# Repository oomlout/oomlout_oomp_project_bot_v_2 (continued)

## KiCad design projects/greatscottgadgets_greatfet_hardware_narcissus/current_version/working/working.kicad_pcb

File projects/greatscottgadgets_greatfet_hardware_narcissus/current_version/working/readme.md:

# greatfet_hardware
 
## summary 
* id: greatscottgadgets_greatfet_hardware_narcissus
* user: greatscottgadgets
* name: greatfet_hardware
* board: narcissus
* repo: https://github.com/greatscottgadgets/greatfet-hardware
* src_file_repo_kicad_pcb: narcissus/narcissus.kicad_pcb
* src_file_repo_kicad_pcb_link: https://github.com/greatscottgadgets/greatfet-hardware/tree/master/narcissus/narcissus.kicad_pcb

* src_file_repo_sch: narcissus/narcissus.sch
* src_file_repo_sch_link: https://github.com/greatscottgadgets/greatfet-hardware/tree/master/narcissus/narcissus.sch
* full details link: https://github.com/oomlout/oomlout_oomp_project_bot_v_2/tree/main/projects/greatscottgadgets_greatfet_hardware_narcissus/current_version/working

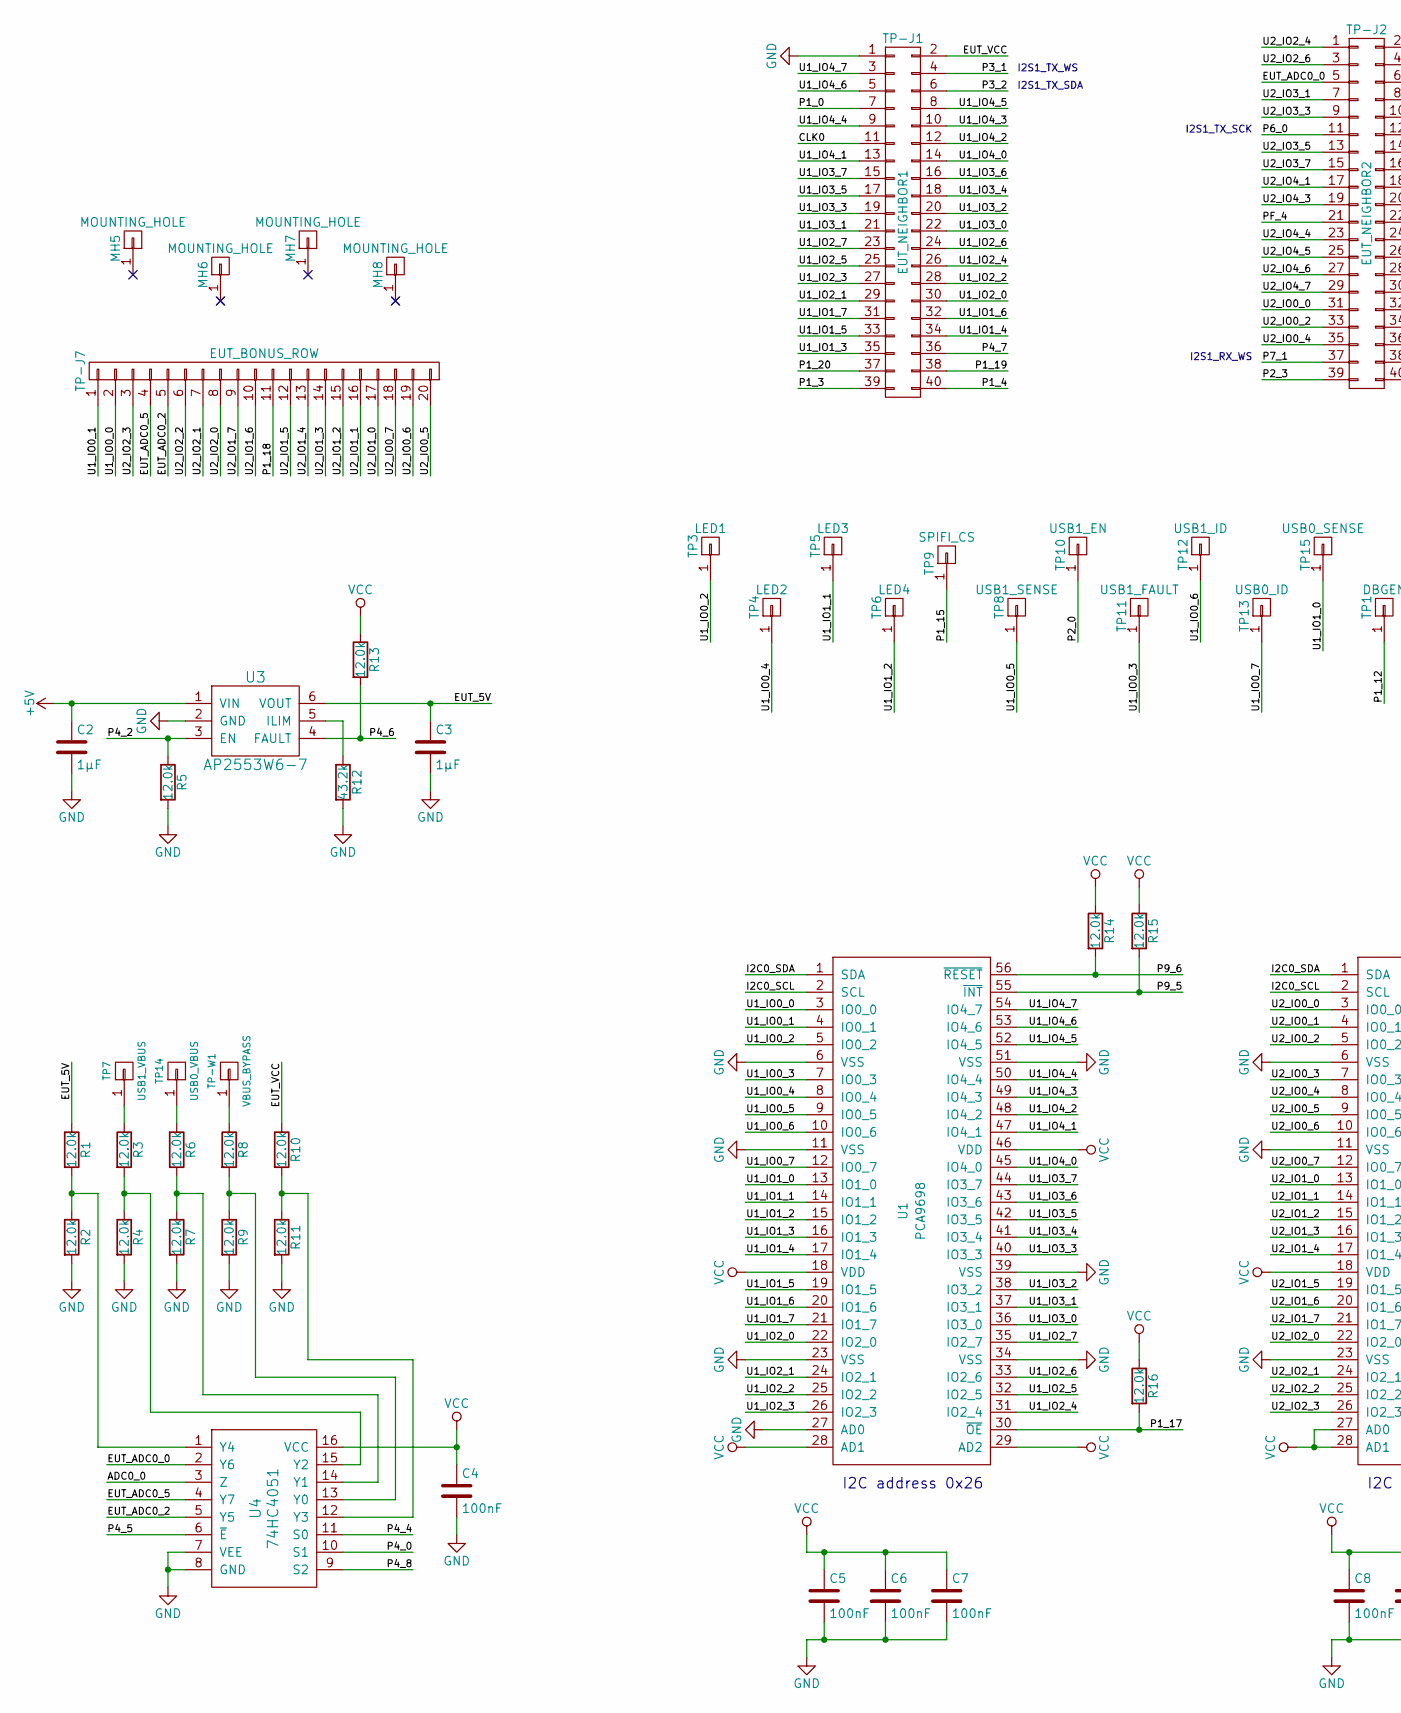
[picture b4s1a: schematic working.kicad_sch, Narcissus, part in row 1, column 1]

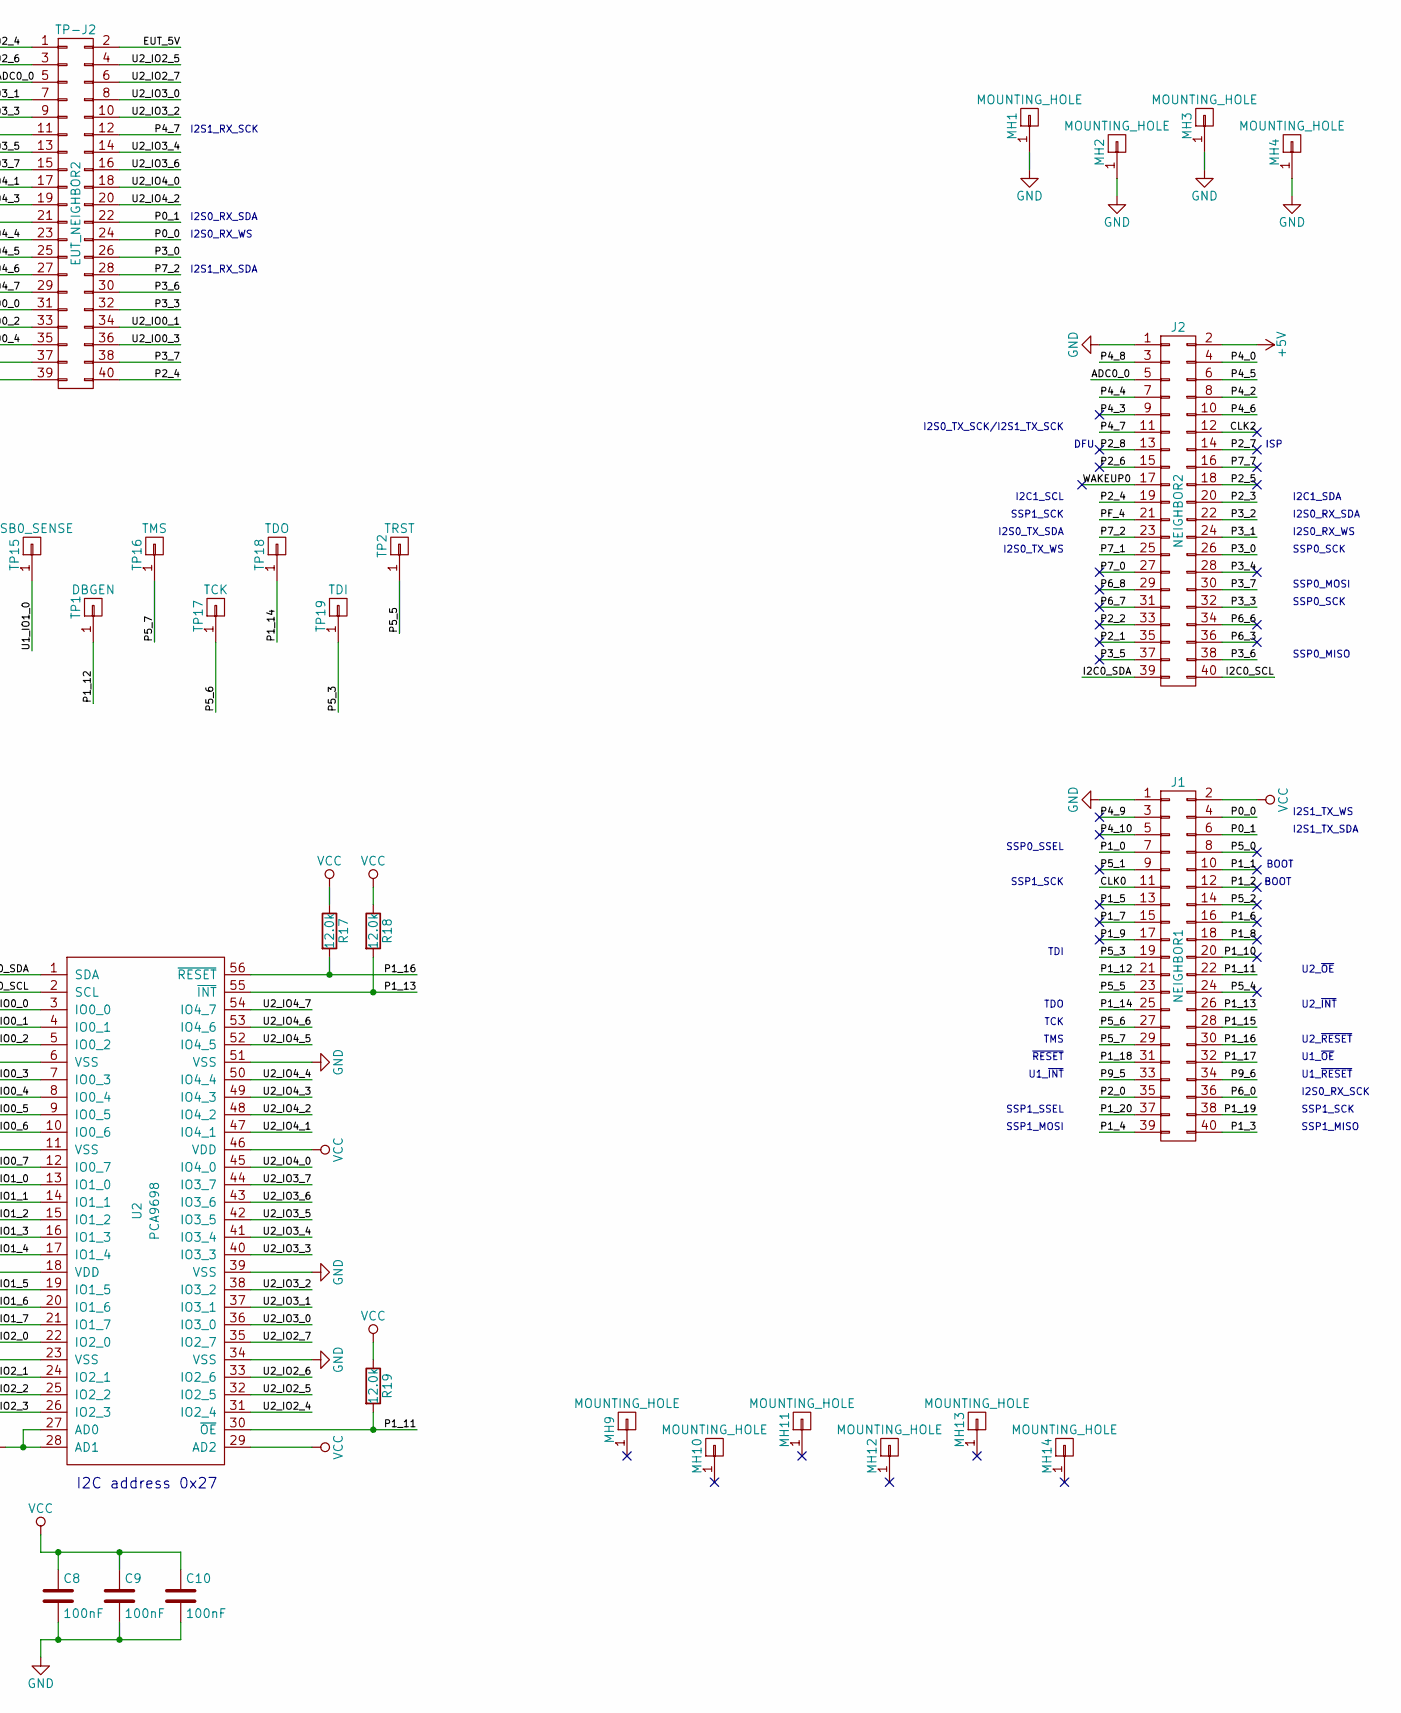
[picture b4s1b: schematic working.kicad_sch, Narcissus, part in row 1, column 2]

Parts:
C2, C3: 1µF; 0603; Part Number CL10A105KP8NNNC
C4, C5, C6, C7, C8, C9, C10: 100nF; 0603; Part Number C0603C104M4RAC
J1: NEIGHBOR1; HEADER-2x20-REVERSE; Part Number SSW-120-01-F-D
J2: NEIGHBOR2; HEADER-2x20-REVERSE; Part Number SSW-120-01-F-D
MH1, MH2, MH3, MH4, MH5, MH6, MH7, MH8, MH9, MH10, MH11, MH12, MH13, MH14: MOUNTING_HOLE; HOLE126MIL-COPPER
R1, R2, R3, R4, R5, R6, R7, R8, R9, R10, R11, R13, R14, R15, R16, R17, R18, R19: 12.0k; 0603; Part Number RMCF0603FT12K0
R12: 43.2k; 0603; Part Number RC0603FR-0743K2L
TP1: DBGEN; HEADER-1x1-TESTPROBE
TP2: TRST; HEADER-1x1-TESTPROBE
TP3: LED1; HEADER-1x1-TESTPROBE
TP4: LED2; HEADER-1x1-TESTPROBE
TP5: LED3; HEADER-1x1-TESTPROBE
TP6: LED4; HEADER-1x1-TESTPROBE
TP7: USB1_VBUS; HEADER-1x1-TESTPROBE
TP8: USB1_SENSE; HEADER-1x1-TESTPROBE
TP9: SPIFI_CS; HEADER-1x1-TESTPROBE
TP10: USB1_EN; HEADER-1x1-TESTPROBE
TP11: USB1_FAULT; HEADER-1x1-TESTPROBE
TP12: USB1_ID; HEADER-1x1-TESTPROBE
TP13: USB0_ID; HEADER-1x1-TESTPROBE
TP14: USB0_VBUS; HEADER-1x1-TESTPROBE
TP15: USB0_SENSE; HEADER-1x1-TESTPROBE
TP16: TMS; HEADER-1x1-TESTPROBE
TP17: TCK; HEADER-1x1-TESTPROBE
TP18: TDO; HEADER-1x1-TESTPROBE
TP19: TDI; HEADER-1x1-TESTPROBE
TP-J1: EUT_NEIGHBOR1; HEADER-2x20-TESTPROBE; Part Number SSW-120-01-F-D
TP-J2: EUT_NEIGHBOR2; HEADER-2x20-TESTPROBE; Part Number SSW-120-01-F-D
TP-J7: EUT_BONUS_ROW; HEADER-1x20-TESTPROBE; Part Number PRPC020SAAN-RC
TP-W1: VBUS_BYPASS; HEADER-1x1-TESTPROBE
U1, U2: PCA9698; TSSOP56; Part Number PCA9698DGG,512
U3: AP2553W6-7; SOT457; Part Number AP2553W6-7
U4: 74HC4051; SOIC16; Part Number 74HC4051D,653

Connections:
+5V: C2.1, J2.2, U3.1 (VIN)
/ADC0_0: J2.5, U4.3 (Z)
/CLK0: J1.11, TP-J1.11
/CLK2: J2.12
/EUT_5V: C3.1, R1.1, TP-J2.2, U3.6 (VOUT)
/EUT_ADC0_0: TP-J2.5, U4.2 (Y6)
/EUT_ADC0_2: TP-J7.5, U4.5 (Y5)
/EUT_ADC0_5: TP-J7.4, U4.4 (Y7)
/EUT_VCC: R10.1, TP-J1.2
/I2C0_SCL: J2.40, U1.2 (SCL), U2.2 (SCL)
/I2C0_SDA: J2.39, U1.1 (SDA), U2.1 (SDA)
/P0_0: J1.4, TP-J2.24
/P0_1: J1.6, TP-J2.22
/P1_0: J1.7, TP-J1.7
/P1_1: J1.10
/P1_2: J1.12
/P1_3: J1.40, TP-J1.39
/P1_4: J1.39, TP-J1.40
/P1_5: J1.13
/P1_6: J1.16
/P1_7: J1.15
/P1_8: J1.18
/P1_9: J1.17
/P1_10: J1.20
/P1_11: J1.22, R19.2, U2.30 (~OE)
/P1_12: J1.21, TP1.1
/P1_13: J1.26, R18.2, U2.55 (~INT)
/P1_14: J1.25, TP18.1
/P1_15: J1.28, TP9.1
/P1_16: J1.30, R17.2, U2.56 (~RESET)
/P1_17: J1.32, R16.2, U1.30 (~OE)
/P1_18: J1.31, TP-J7.11
/P1_19: J1.38, TP-J1.38
/P1_20: J1.37, TP-J1.37
/P2_0: J1.35, TP10.1
/P2_1: J2.35
/P2_2: J2.33
/P2_3: J2.20, TP-J2.39
/P2_4: J2.19, TP-J2.40
/P2_5: J2.18
/P2_6: J2.15
/P2_7: J2.14
/P2_8: J2.13
/P3_0: J2.26, TP-J2.26
/P3_1: J2.24, TP-J1.4
/P3_2: J2.22, TP-J1.6
/P3_3: J2.32, TP-J2.32
/P3_4: J2.28
/P3_5: J2.37
/P3_6: J2.38, TP-J2.30
/P3_7: J2.30, TP-J2.38
/P4_0: J2.4, U4.10 (S1)
/P4_2: J2.8, R5.1, U3.3 (EN)
/P4_3: J2.9
/P4_4: J2.7, U4.11 (S0)
/P4_5: J2.6, U4.6 (~E)
/P4_6: J2.10, R13.2, U3.4 (FAULT)
/P4_7: J2.11, TP-J1.36, TP-J2.12
/P4_8: J2.3, U4.9 (S2)
/P4_9: J1.3
/P4_10: J1.5
/P5_0: J1.8
/P5_1: J1.9
/P5_2: J1.14
/P5_3: J1.19, TP19.1
/P5_4: J1.24
/P5_5: J1.23, TP2.1
/P5_6: J1.27, TP17.1
/P5_7: J1.29, TP16.1
/P6_0: J1.36, TP-J2.11
/P6_3: J2.36
/P6_6: J2.34
/P6_7: J2.31
/P6_8: J2.29
/P7_0: J2.27
/P7_1: J2.25, TP-J2.37
/P7_2: J2.23, TP-J2.28
/P7_7: J2.16
/P9_5: J1.33, R15.2, U1.55 (~INT)
/P9_6: J1.34, R14.2, U1.56 (~RESET)
/PF_4: J2.21, TP-J2.21
/U1_IO0_0: TP-J7.2, U1.3 (IO0_0)
/U1_IO0_1: TP-J7.1, U1.4 (IO0_1)
/U1_IO0_2: TP3.1, U1.5 (IO0_2)
/U1_IO0_3: TP11.1, U1.7 (IO0_3)
/U1_IO0_4: TP4.1, U1.8 (IO0_4)
/U1_IO0_5: TP8.1, U1.9 (IO0_5)
/U1_IO0_6: TP12.1, U1.10 (IO0_6)
/U1_IO0_7: TP13.1, U1.12 (IO0_7)
/U1_IO1_0: TP15.1, U1.13 (IO1_0)
/U1_IO1_1: TP5.1, U1.14 (IO1_1)
/U1_IO1_2: TP6.1, U1.15 (IO1_2)
/U1_IO1_3: TP-J1.35, U1.16 (IO1_3)
/U1_IO1_4: TP-J1.34, U1.17 (IO1_4)
/U1_IO1_5: TP-J1.33, U1.19 (IO1_5)
/U1_IO1_6: TP-J1.32, U1.20 (IO1_6)
/U1_IO1_7: TP-J1.31, U1.21 (IO1_7)
/U1_IO2_0: TP-J1.30, U1.22 (IO2_0)
/U1_IO2_1: TP-J1.29, U1.24 (IO2_1)
/U1_IO2_2: TP-J1.28, U1.25 (IO2_2)
/U1_IO2_3: TP-J1.27, U1.26 (IO2_3)
/U1_IO2_4: TP-J1.26, U1.31 (IO2_4)
/U1_IO2_5: TP-J1.25, U1.32 (IO2_5)
/U1_IO2_6: TP-J1.24, U1.33 (IO2_6)
/U1_IO2_7: TP-J1.23, U1.35 (IO2_7)
/U1_IO3_0: TP-J1.22, U1.36 (IO3_0)
/U1_IO3_1: TP-J1.21, U1.37 (IO3_1)
/U1_IO3_2: TP-J1.20, U1.38 (IO3_2)
/U1_IO3_3: TP-J1.19, U1.40 (IO3_3)
/U1_IO3_4: TP-J1.18, U1.41 (IO3_4)
/U1_IO3_5: TP-J1.17, U1.42 (IO3_5)
/U1_IO3_6: TP-J1.16, U1.43 (IO3_6)
/U1_IO3_7: TP-J1.15, U1.44 (IO3_7)
/U1_IO4_0: TP-J1.14, U1.45 (IO4_0)
/U1_IO4_1: TP-J1.13, U1.47 (IO4_1)
/U1_IO4_2: TP-J1.12, U1.48 (IO4_2)
/U1_IO4_3: TP-J1.10, U1.49 (IO4_3)
/U1_IO4_4: TP-J1.9, U1.50 (IO4_4)
/U1_IO4_5: TP-J1.8, U1.52 (IO4_5)
/U1_IO4_6: TP-J1.5, U1.53 (IO4_6)
/U1_IO4_7: TP-J1.3, U1.54 (IO4_7)
/U2_IO0_0: TP-J2.31, U2.3 (IO0_0)
/U2_IO0_1: TP-J2.34, U2.4 (IO0_1)
/U2_IO0_2: TP-J2.33, U2.5 (IO0_2)
/U2_IO0_3: TP-J2.36, U2.7 (IO0_3)
/U2_IO0_4: TP-J2.35, U2.8 (IO0_4)
/U2_IO0_5: TP-J7.20, U2.9 (IO0_5)
/U2_IO0_6: TP-J7.19, U2.10 (IO0_6)
/U2_IO0_7: TP-J7.18, U2.12 (IO0_7)
/U2_IO1_0: TP-J7.17, U2.13 (IO1_0)
/U2_IO1_1: TP-J7.16, U2.14 (IO1_1)
/U2_IO1_2: TP-J7.15, U2.15 (IO1_2)
/U2_IO1_3: TP-J7.14, U2.16 (IO1_3)
/U2_IO1_4: TP-J7.13, U2.17 (IO1_4)
/U2_IO1_5: TP-J7.12, U2.19 (IO1_5)
/U2_IO1_6: TP-J7.10, U2.20 (IO1_6)
/U2_IO1_7: TP-J7.9, U2.21 (IO1_7)
/U2_IO2_0: TP-J7.8, U2.22 (IO2_0)
/U2_IO2_1: TP-J7.7, U2.24 (IO2_1)
/U2_IO2_2: TP-J7.6, U2.25 (IO2_2)
/U2_IO2_3: TP-J7.3, U2.26 (IO2_3)
/U2_IO2_4: TP-J2.1, U2.31 (IO2_4)
/U2_IO2_5: TP-J2.4, U2.32 (IO2_5)
/U2_IO2_6: TP-J2.3, U2.33 (IO2_6)
/U2_IO2_7: TP-J2.6, U2.35 (IO2_7)
/U2_IO3_0: TP-J2.8, U2.36 (IO3_0)
/U2_IO3_1: TP-J2.7, U2.37 (IO3_1)
/U2_IO3_2: TP-J2.10, U2.38 (IO3_2)
/U2_IO3_3: TP-J2.9, U2.40 (IO3_3)
/U2_IO3_4: TP-J2.14, U2.41 (IO3_4)
/U2_IO3_5: TP-J2.13, U2.42 (IO3_5)
/U2_IO3_6: TP-J2.16, U2.43 (IO3_6)
/U2_IO3_7: TP-J2.15, U2.44 (IO3_7)
/U2_IO4_0: TP-J2.18, U2.45 (IO4_0)
/U2_IO4_1: TP-J2.17, U2.47 (IO4_1)
/U2_IO4_2: TP-J2.20, U2.48 (IO4_2)
/U2_IO4_3: TP-J2.19, U2.49 (IO4_3)
/U2_IO4_4: TP-J2.23, U2.50 (IO4_4)
/U2_IO4_5: TP-J2.25, U2.52 (IO4_5)
/U2_IO4_6: TP-J2.27, U2.53 (IO4_6)
/U2_IO4_7: TP-J2.29, U2.54 (IO4_7)
/WAKEUP0: J2.17
GND: C2.2, C3.2, C4.2, C5.2, C6.2, C7.2, C8.2, C9.2, C10.2, J1.1, J2.1, MH1.1, MH2.1, MH3.1, MH4.1, R2.2, R4.2, R5.2, R7.2, R9.2, R11.2, R12.2, TP-J1.1, U1.6 (VSS), U1.11 (VSS), U1.23 (VSS), U1.27 (AD0), U1.34 (VSS), U1.39 (VSS), U1.51 (VSS), U2.6 (VSS), U2.11 (VSS), U2.23 (VSS), U2.34 (VSS), U2.39 (VSS), U2.51 (VSS), U3.2 (GND), U4.7 (VEE), U4.8 (GND)
unnamed: R1.2, R2.1, U4.1 (Y4)
unnamed: R3.1, TP7.1
unnamed: R3.2, R4.1, U4.15 (Y2)
unnamed: R6.1, TP14.1
unnamed: R6.2, R7.1, U4.14 (Y1)
unnamed: R8.1, TP-W1.1
unnamed: R8.2, R9.1, U4.13 (Y0)
unnamed: R10.2, R11.1, U4.12 (Y3)
unnamed: R12.1, U3.5 (ILIM)
VCC: C4.1, C5.1, C6.1, C7.1, C8.1, C9.1, C10.1, J1.2, R13.1, R14.1, R15.1, R16.1, R17.1, R18.1, R19.1, U1.18 (VDD), U1.28 (AD1), U1.29 (AD2), U1.46 (VDD), U2.18 (VDD), U2.27 (AD0), U2.28 (AD1), U2.29 (AD2), U2.46 (VDD), U4.16 (VCC)

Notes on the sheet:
I2S1_RX_SCK
U1_~{OE}
SSP0_MOSI
SSP1_MOSI
TDO
I2S0_RX_WS
U2_~{OE}
TMS
~{RESET}
DFU
SSP0_SCK
U2_~{RESET}
SSP1_SCK
BOOT
I2S0_RX_SDA
I2C1_SDA
TDI
I2S1_TX_WS
I2S0_TX_SDA
U2_~{INT}
I2C address 0x26
U1_~{RESET}
I2S0_TX_SCK/I2S1_TX_SCK
I2C1_SCL
SSP1_MISO
I2S0_RX_SCK
SSP0_SSEL
I2C address 0x27
I2S1_RX_SDA
I2S1_TX_SCK
SSP0_MISO
I2S0_TX_WS
I2S1_RX_WS
SSP1_SSEL
ISP
TCK
U1_~{INT}
I2S1_TX_SDA

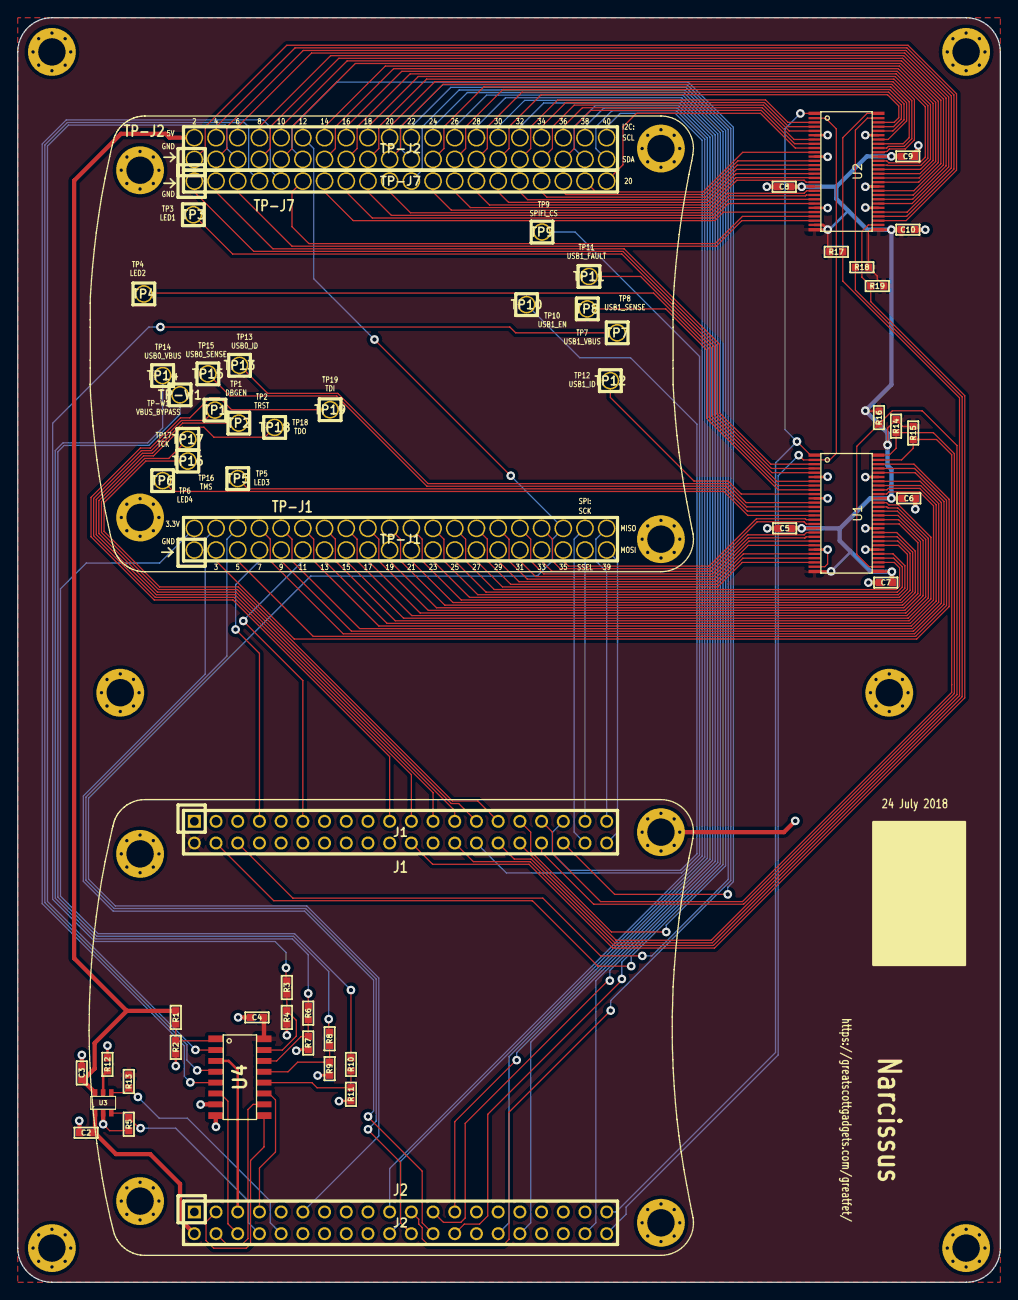
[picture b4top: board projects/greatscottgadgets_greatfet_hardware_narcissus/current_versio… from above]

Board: 2 copper layers, 115.0 x 148.0 mm, 71 parts (0 on the bottom side), 142 nets.

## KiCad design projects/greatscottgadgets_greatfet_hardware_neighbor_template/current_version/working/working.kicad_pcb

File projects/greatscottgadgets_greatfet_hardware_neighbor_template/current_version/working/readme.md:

# greatfet_hardware
 
## summary 
* id: greatscottgadgets_greatfet_hardware_neighbor_template
* user: greatscottgadgets
* name: greatfet_hardware
* board: neighbor_template
* repo: https://github.com/greatscottgadgets/greatfet-hardware
* src_file_repo_kicad_pcb: neighbor-template/neighbor-template.kicad_pcb
* src_file_repo_kicad_pcb_link: https://github.com/greatscottgadgets/greatfet-hardware/tree/master/neighbor-template/neighbor-template.kicad_pcb

* src_file_repo_sch: neighbor-template/neighbor-template.sch
* src_file_repo_sch_link: https://github.com/greatscottgadgets/greatfet-hardware/tree/master/neighbor-template/neighbor-template.sch
* full details link: https://github.com/oomlout/oomlout_oomp_project_bot_v_2/tree/main/projects/greatscottgadgets_greatfet_hardware_neighbor_template/current_version/working

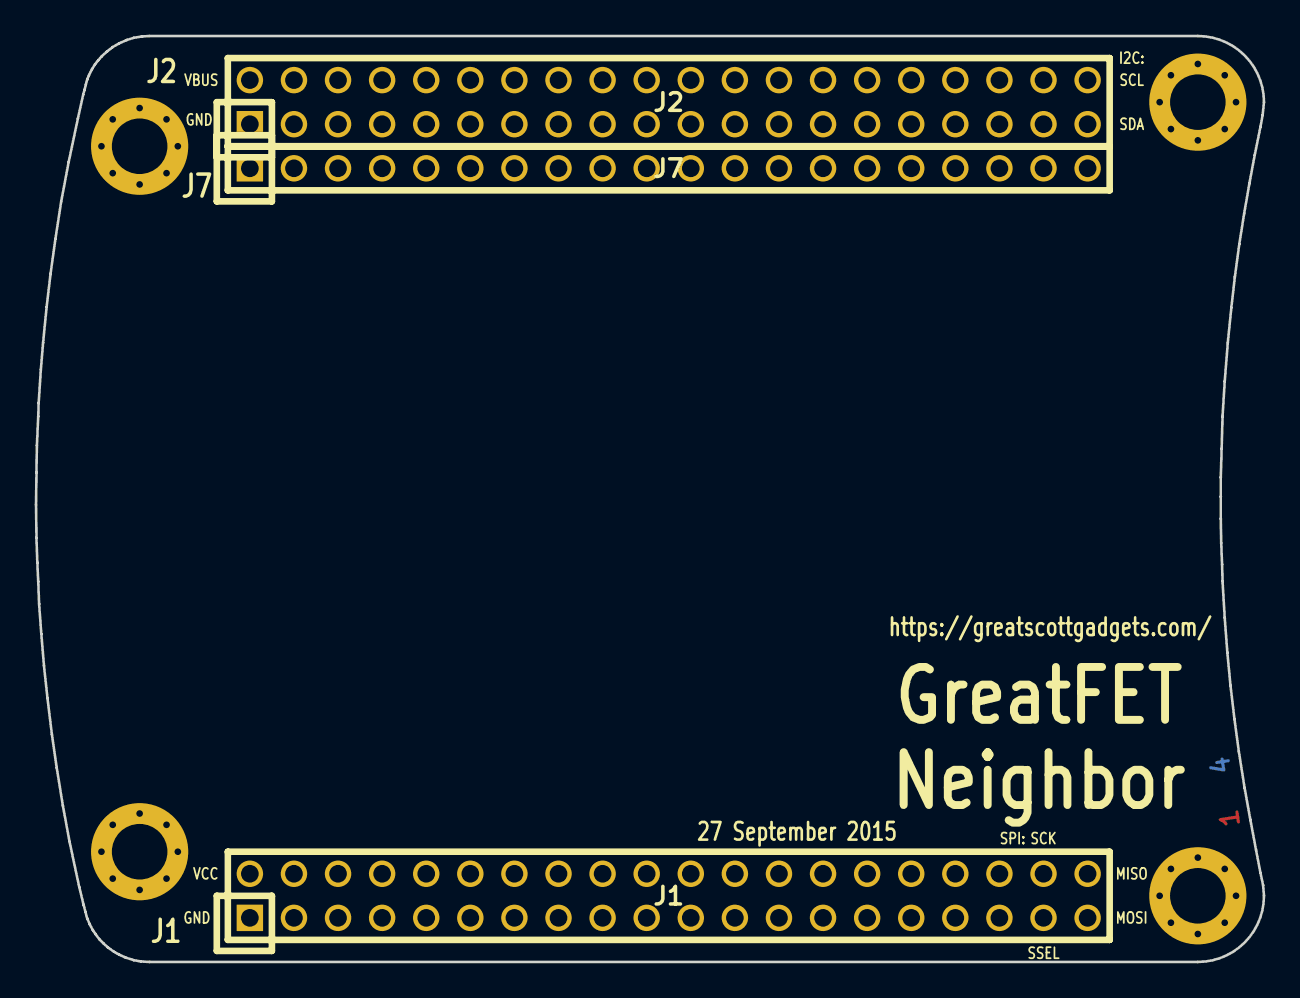
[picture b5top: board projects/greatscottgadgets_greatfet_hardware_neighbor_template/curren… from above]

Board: 4 copper layers, 70.7 x 53.3 mm, 7 parts (0 on the bottom side), 2 nets, no tracks yet.

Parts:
J1: NEIGHBOR1; HEADER-2x20
J2: NEIGHBOR2; HEADER-2x20
J7: BONUS_ROW; HEADER-1x20
MH1, MH2, MH3, MH4: MOUNTING_HOLE; HOLE126MIL-COPPER

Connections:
GND: J1.1, J2.1, J7.1, J7.10, J7.19, MH1.1, MH2.1, MH3.1, MH4.1
VCC: J1.2, J7.20

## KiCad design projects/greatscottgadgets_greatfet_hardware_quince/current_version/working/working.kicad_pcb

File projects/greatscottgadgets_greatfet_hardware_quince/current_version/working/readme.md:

# greatfet_hardware
 
## summary 
* id: greatscottgadgets_greatfet_hardware_quince
* user: greatscottgadgets
* name: greatfet_hardware
* board: quince
* repo: https://github.com/greatscottgadgets/greatfet-hardware
* src_file_repo_kicad_pcb: quince/quince.kicad_pcb
* src_file_repo_kicad_pcb_link: https://github.com/greatscottgadgets/greatfet-hardware/tree/master/quince/quince.kicad_pcb

* src_file_repo_sch: quince/quince.sch
* src_file_repo_sch_link: https://github.com/greatscottgadgets/greatfet-hardware/tree/master/quince/quince.sch
* full details link: https://github.com/oomlout/oomlout_oomp_project_bot_v_2/tree/main/projects/greatscottgadgets_greatfet_hardware_quince/current_version/working

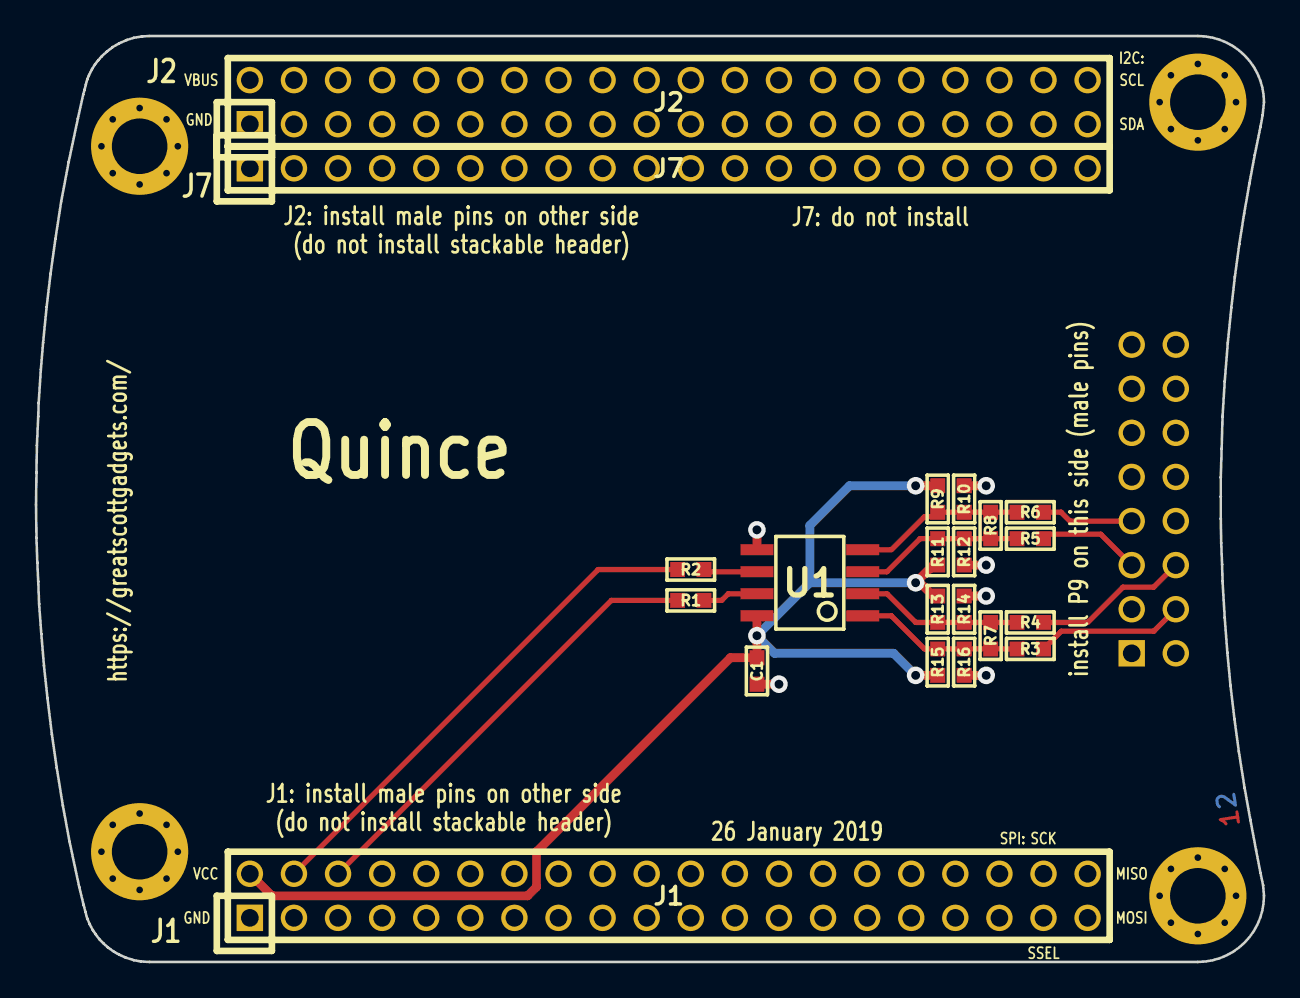
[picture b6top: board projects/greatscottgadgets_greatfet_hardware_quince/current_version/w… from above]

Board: 2 copper layers, 70.7 x 53.3 mm, 26 parts (1 on the bottom side), 14 nets.

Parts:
C1: C; 0603
J1: NEIGHBOR1; HEADER-2x20
J2: NEIGHBOR2; HEADER-2x20
J7: BONUS_ROW; HEADER-1x20
MH1, MH2, MH3, MH4: MOUNTING_HOLE; HOLE126MIL-COPPER
P9: BASEBAND; HEADER-2x8
R1, R2, R3, R4, R5, R6: 0; 0603
R7, R8, R9, R10, R11, R12, R13, R14, R15, R16: R; 0603
U1: TLV3502; SOIC8-154

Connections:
/+IN_A: R3.1, R7.1, R15.2, R16.1, U1.1
/+IN_B: R5.1, R8.1, R11.2, R12.1, U1.3
/-IN_A: R4.1, R7.2, R13.2, R14.1, U1.2
/-IN_B: R6.1, R8.2, R9.2, R10.1, U1.4
/OUT_A: R1.2, U1.7
/OUT_B: R2.2, U1.6
/P0_0: J1.4, R2.1
/P0_1: J1.6, R1.1
/RXBBI+: P9.7, R6.2
/RXBBI-: P9.5, R5.2
/RXBBQ+: P9.6, R4.2
/RXBBQ-: P9.4, R3.2
GND: C1.1, J1.1, J2.1, J7.1, J7.10, J7.19, MH1.1, MH2.1, MH3.1, MH4.1, P9.1, P9.2, P9.3, P9.8, P9.9, P9.14, P9.15, P9.16, R10.2, R12.2, R14.2, R16.2, U1.5
VCC: C1.2, J1.2, R9.1, R11.1, R13.1, R15.1, U1.8

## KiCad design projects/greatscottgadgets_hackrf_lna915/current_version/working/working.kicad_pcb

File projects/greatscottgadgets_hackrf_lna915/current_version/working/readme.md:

# hackrf
 
## summary 
* id: greatscottgadgets_hackrf_lna915
* user: greatscottgadgets
* name: hackrf
* board: lna915
* repo: https://github.com/greatscottgadgets/hackrf
* src_file_repo_kicad_pcb: hardware/LNA915/LNA915.kicad_pcb
* src_file_repo_kicad_pcb_link: https://github.com/greatscottgadgets/hackrf/tree/master/hardware/LNA915/LNA915.kicad_pcb
* src_file_repo_kicad_sch: hardware/hackrf-one/baseband.kicad_sch
* src_file_repo_kicad_sch_link: https://github.com/greatscottgadgets/hackrf/tree/master/hardware/hackrf-one/baseband.kicad_sch

* src_file_repo_sch: hardware/LNA915/LNA915.sch
* src_file_repo_sch_link: https://github.com/greatscottgadgets/hackrf/tree/master/hardware/LNA915/LNA915.sch
* full details link: https://github.com/oomlout/oomlout_oomp_project_bot_v_2/tree/main/projects/greatscottgadgets_hackrf_lna915/current_version/working

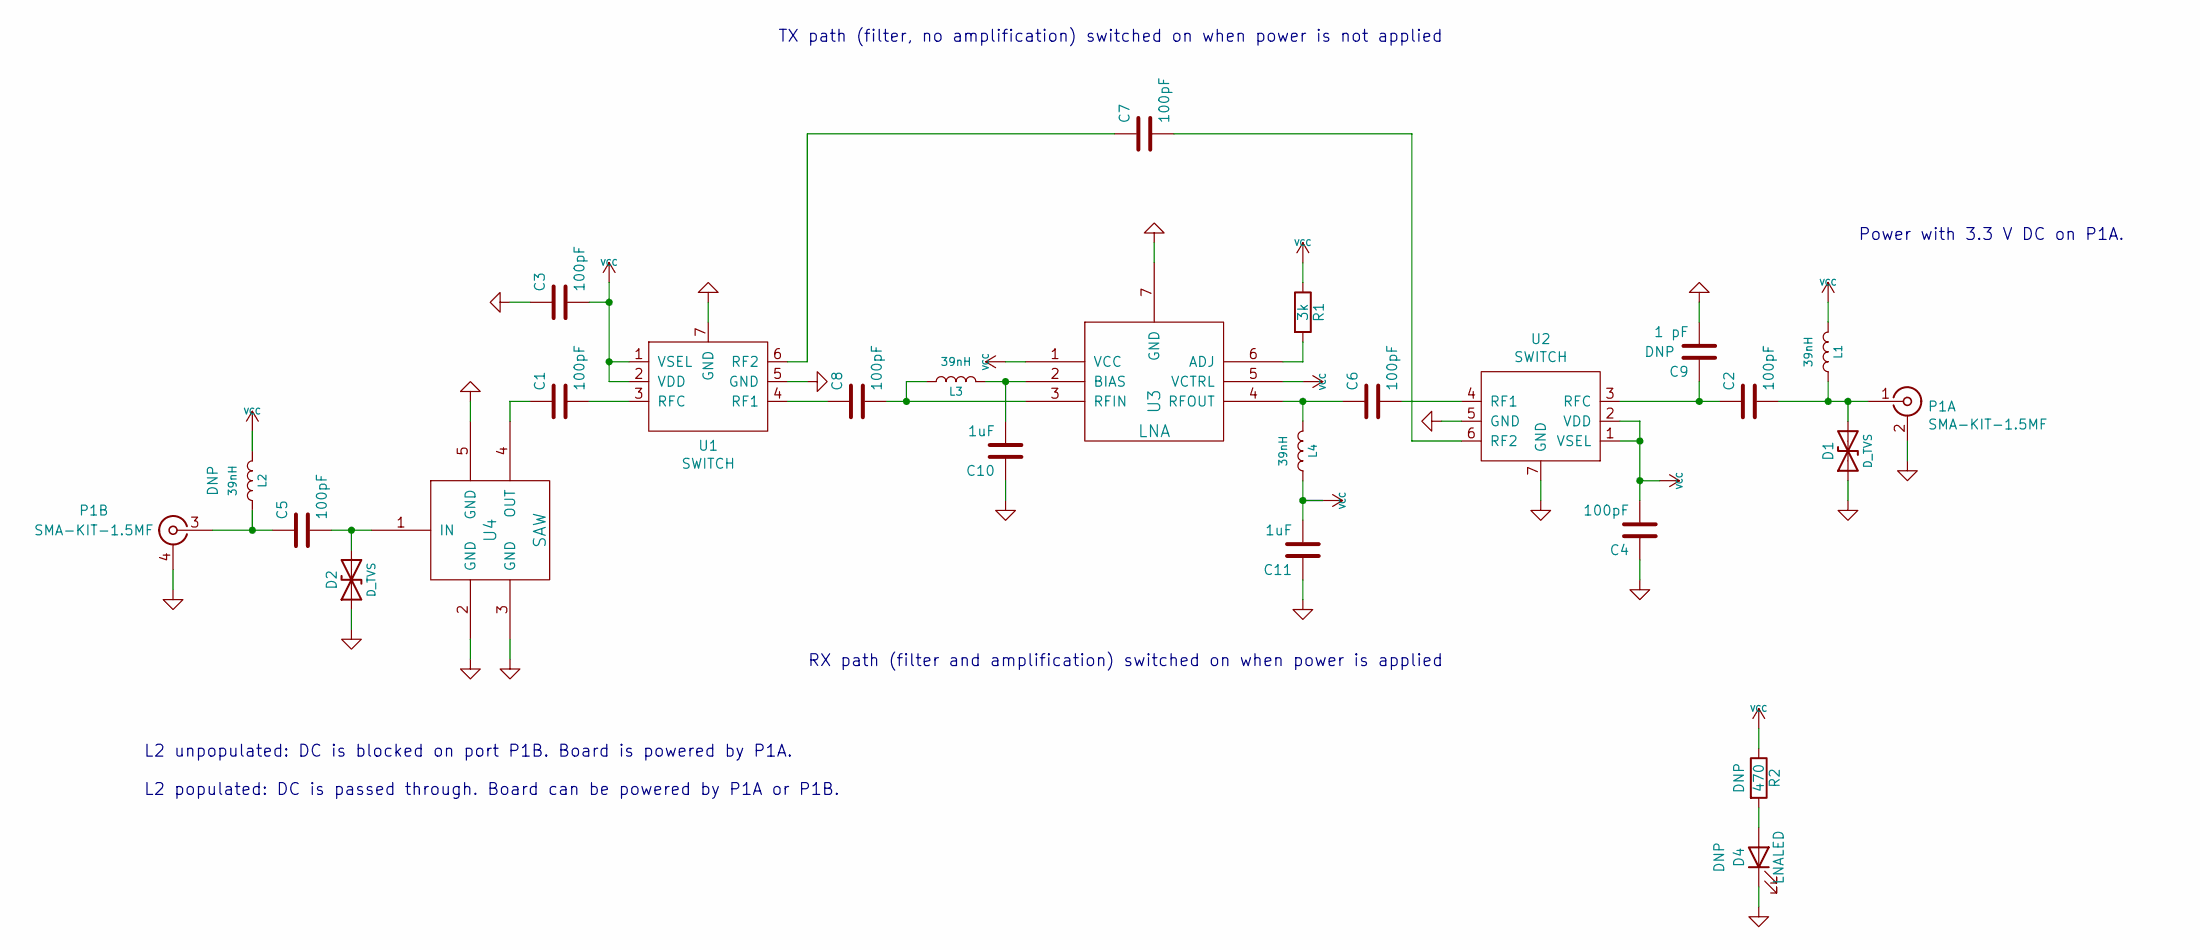
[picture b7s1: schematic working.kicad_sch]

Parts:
C1, C2, C3, C4, C5, C6, C7, C8: 100pF; 0402; Part Number GCM1555C1H101JA16
C9: 1 pF; 0402
C10, C11: 1uF; 0402; Part Number LMK105BJ105KV-F
D1, D2: D_TVS; 0402; Part Number LXES15AAA1-153
D4: LNALED; 0402
L1, L2, L3, L4: 39nH; 0402; Part Number HK100539NJ-T
P1: SMA-KIT-1.5MF; Part Number SMA-KIT-1.5MF
R1: 3k; 0402; Part Number RMCF0402FT3K00
R2: 470; 0402; Part Number RMCF0402JT470R
U1, U2: SWITCH; GRF6011; Part Number GRF6011
U3: LNA; TSLP-7-1; Part Number BGB 741L7ESD E6327
U4: SAW; F5Q; Part Number FAR-F5QA-915M00-M2AK-J

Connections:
GND: C3.1, C4.1, C9.2, C10.1, C11.1, D1.1 (A1), D2.1 (A1), D4.1 (K), P1.2 (SHIELD), P1.4 (SHIELD), U1.5 (GND), U1.7 (GND), U2.5 (GND), U2.7 (GND), U3.7 (GND), U4.2 (GND), U4.3 (GND), U4.5 (GND)
unnamed: C1.1, U4.4 (OUT)
unnamed: C1.2, U1.3 (RFC)
unnamed: C2.1, C9.1, U2.3 (RFC)
unnamed: C2.2, D1.2 (A2), L1.1, P1.1 (RF)
unnamed: C5.1, L2.1, P1.3 (RF)
unnamed: C5.2, D2.2 (A2), U4.1 (IN)
unnamed: C6.1, L4.2, U3.4 (RFOUT)
unnamed: C6.2, U2.4 (RF1)
unnamed: C7.1, U1.6 (RF2)
unnamed: C7.2, U2.6 (RF2)
unnamed: C8.1, U1.4 (RF1)
unnamed: C8.2, L3.1, U3.3 (RFIN)
unnamed: C10.2, L3.2, U3.2 (BIAS)
unnamed: D4.2 (A), R2.2
unnamed: R1.2, U3.6 (ADJ)
VCC: C3.2, C4.2, C11.2, L1.2, L2.2, L4.1, R1.1, R2.1, U1.1 (VSEL), U1.2 (VDD), U2.1 (VSEL), U2.2 (VDD), U3.1 (VCC), U3.5 (VCTRL)

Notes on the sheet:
Power with 3.3 V DC on P1A.
L2 unpopulated: DC is blocked on port P1B. Board is powered by P1A. L2 populated: DC is passed through. Board can be powered by P1A or P1B.
TX path (filter, no amplification) switched on when power is not applied
RX path (filter and amplification) switched on when power is applied

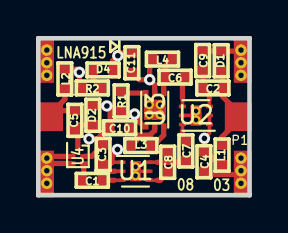
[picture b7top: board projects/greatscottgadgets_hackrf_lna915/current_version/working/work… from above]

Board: 4 copper layers, 11.7 x 8.7 mm, 25 parts (0 on the bottom side), 17 nets.
